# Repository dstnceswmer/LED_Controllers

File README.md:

# LED_Controllers
Controller boards for leds

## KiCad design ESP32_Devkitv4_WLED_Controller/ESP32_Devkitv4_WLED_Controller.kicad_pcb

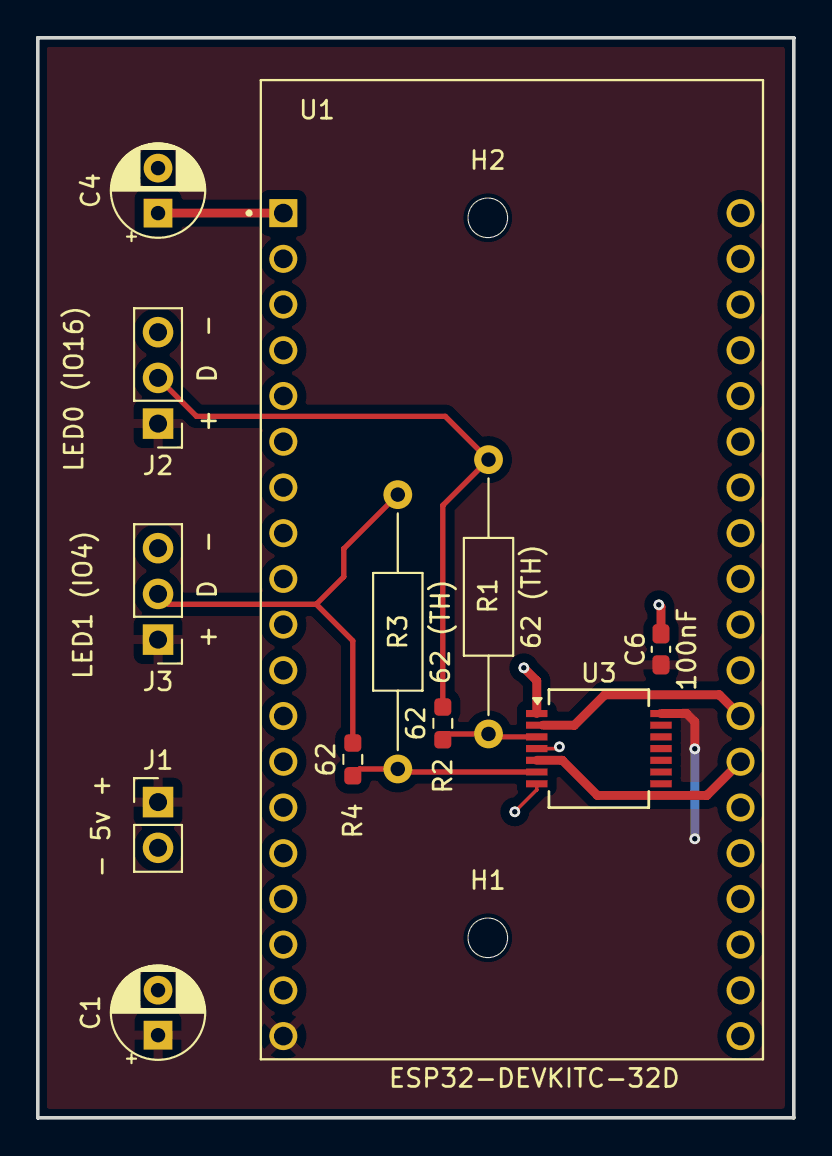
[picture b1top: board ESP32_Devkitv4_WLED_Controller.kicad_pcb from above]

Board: 2 copper layers, 42.0 x 60.0 mm, 14 parts (0 on the bottom side), 9 nets.

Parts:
C1, C4: 470uF (TH); CP_Radial_D5.0mm_P2.50mm
C6: 100nF; C_0603_1608Metric_Pad1.08x0.95mm_HandSolder
H1, H2: MountingHole; MountingHole_2.2mm_M2
J1: - 5v +; PinHeader_1x02_P2.54mm_Vertical
J2: LED0 (IO16); PinHeader_1x03_P2.54mm_Vertical
J3: LED1 (IO4); PinHeader_1x03_P2.54mm_Vertical
R1, R3: 62 (TH); R_Axial_DIN0207_L6.3mm_D2.5mm_P15.24mm_Horizontal
R2, R4: 62; R_0603_1608Metric_Pad0.98x0.95mm_HandSolder
U1: ESP32-DEVKITC-32D; MODULE_ESP32-DEVKITC-32D
U3: 74AHCT125; SSOP-14_5.3x6.2mm_P0.65mm

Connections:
+3.3V: C4.1, U1.J2-1 (3V3)
+5V: C1.1, C6.1, J1.1, J2.1, J3.1, U1.J2-19 (EXT_5V), U3.14 (VCC)
D0: J2.2, R1.2, R2.2
D0_uC: U1.J3-12 (IO16), U3.2
D1: J3.2, R3.2, R4.2
D1_uC: U1.J3-13 (IO4), U3.5
GND: C1.2, C4.2, C6.2, J1.2, J2.3, J3.3, U1.J2-14 (GND1), U1.J3-1 (GND3), U1.J3-7 (GND2), U3.1, U3.4, U3.7 (GND)
unnamed: R1.1, R2.1, U3.3
unnamed: R3.1, R4.1, U3.6

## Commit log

2026-03-03 ESP32_Devkit4_WLED_Controller: Initial commit
2026-03-10 Reorg by MCU
2026-03-13 Add new XIAO-C3 board
2026-03-26 add kicad libraries
2026-03-26 move into project folder under modules
2026-03-26 use env vars for symbol libs
2026-03-26 ignore fp-info-cache
2026-03-26 Add my mcu footprints to XIAO32_LED
2026-03-26 XIAO32_LED: Initial Add of components to sch
2026-03-31 Initial wiring of Power and Connectors pages
2026-04-05 XIAO32_LED: MCU wired up
2026-04-15 XIAO32_LED: Convert sch to hierarchical pins
